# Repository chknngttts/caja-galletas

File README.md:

# caja-galletas

> *Caja de ruido en proceso*
>
> *Todas las versiones de KiCad están en sus carpetas propias*

-------------------

- ### Ideas y specs

> *La idea es tener esta PCB en una caja de galletas*
> 
> *La placa en sí ya tiene efectos integrados como reverb y un Muff Fuzz*
> 
> *La caja se conecta a un parlante o pc con Jack 3.5mm*
> 
> *Y como alimentación también cuenta con un Jack 3.5mm*
> 

  - Dentro de la caja hay:
    - Regulador de voltaje **``(9V -----> 5V)``**
      - VBUS
    - Reverb **``(PT2399)``**
      - *Switch para tener feedback*
    - Pre-Amp / Amp **``(TL072)``**
    - Muff Fuzz **``(2N5088)``**

-  ## **v2**

- ### esquematico v2

-  

-  El esqumatico del PT2399 es el "Boy in Well" con un mod de DIY Guitar Pedals:
    - https://youtu.be/9sHnaUfTWug?si=lqVHKw3zSinBoRW7&t=106 (1:46 - 4:46)
    - Muestra que cortando la conexión de un potenciómetro (RV7) con un switch y bajando el valor de una resistencia (R37), permite que la señal no se filtre (y no pierda info) para que llegue de vuelta al PT2399 haciendo repeats infinitos
      - https://www.diyguitarpedals.com.au/shop/boms/Boy%20in%20Well.pdf (Esquematico original sin switch) (Pagina 30)
    - En KiCad al hacer el ERC no me arroja errores
      - Solo 2 avisos de simbolos que modifiqué para hacer más facil el esquematico
      - En la PBC tampoco me muestra errores de conexión
        - Si quiero cambiar el tamaño y orden de la placa
          - Más rectangular y ahorrar espacio
         
-------------------
- Pre-Amp:         
  - 
  - El Amp que tomé de referencia, es el mismo que el de [maincra](https://github.com/disenoUDP/dis8644-2026-1-procesos-2/tree/main/00-proyecto-02/grupo-01)
    - Con los cambios para hacer más sensible el piezo (R4 y R5)
    - Eso sí, ahora usando ambos OP-Amps

- Muff Fuzz:
  - 
  - El efecto "Muff Fuzz" lo saqué de esta pagina:
    - https://beavisaudio.com/beavisboard/projects/bbp_MuffFuzz.pdf
 
-------------------

- ### pcb v2

- 
  - Tengo que arreglar las vías *(?)*
    - Sin querer use el tamaño predeterminado, no se si eso vaya a ser un problema
  - La huella de los 2N5088 y 78L05 tienen uno externo a la biblioteca de KiCad
    - Los cambié por uno de la biblioteca default en el v3
      - Además de corregir un alivio termico que no nombraban en los errores pero si era preocupante
- 
  - Hay espacio vacío que me permite re-ordenar los componentes y achicar el tamaño de la PCB
 
-------------------
 
- #### *v3 fueron arreglos minimos de huellas*

-------------------

- ## **v4**

- ### esquematico v4
  - 
    - igual que v2 pero con Jack 3.5mm a cambio del Terminal Block
 
-------------------
 
- ### pcb v4

- 
  - Cambié las vías al tamaño que nos recomendaros en taller
    - Optimicé la posición de los componentes para usar el espacio vacío
  - Añadí Mounting Holes M3
  - Al ver los errores solo mostraba problemas de la serigrafía
    - Nada con alivios termicos
- 
- 
  - Prefiero el color negro a rosado/morado

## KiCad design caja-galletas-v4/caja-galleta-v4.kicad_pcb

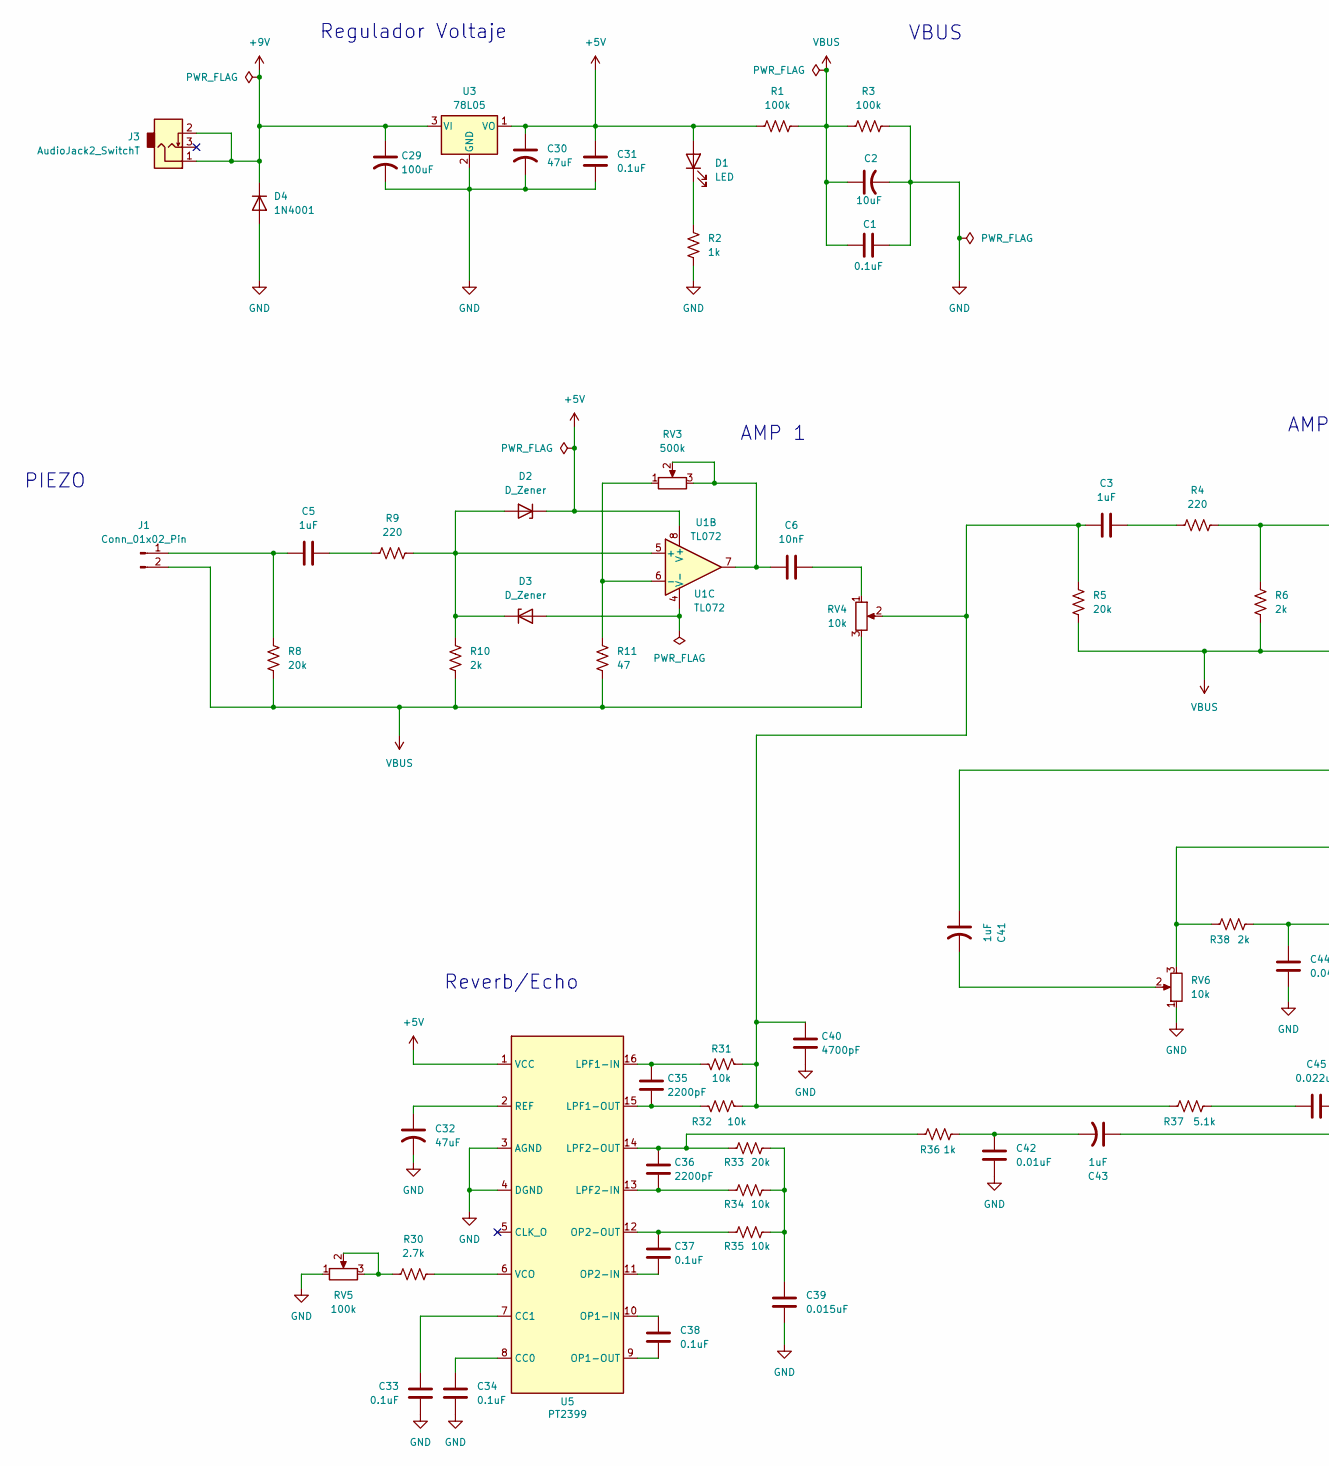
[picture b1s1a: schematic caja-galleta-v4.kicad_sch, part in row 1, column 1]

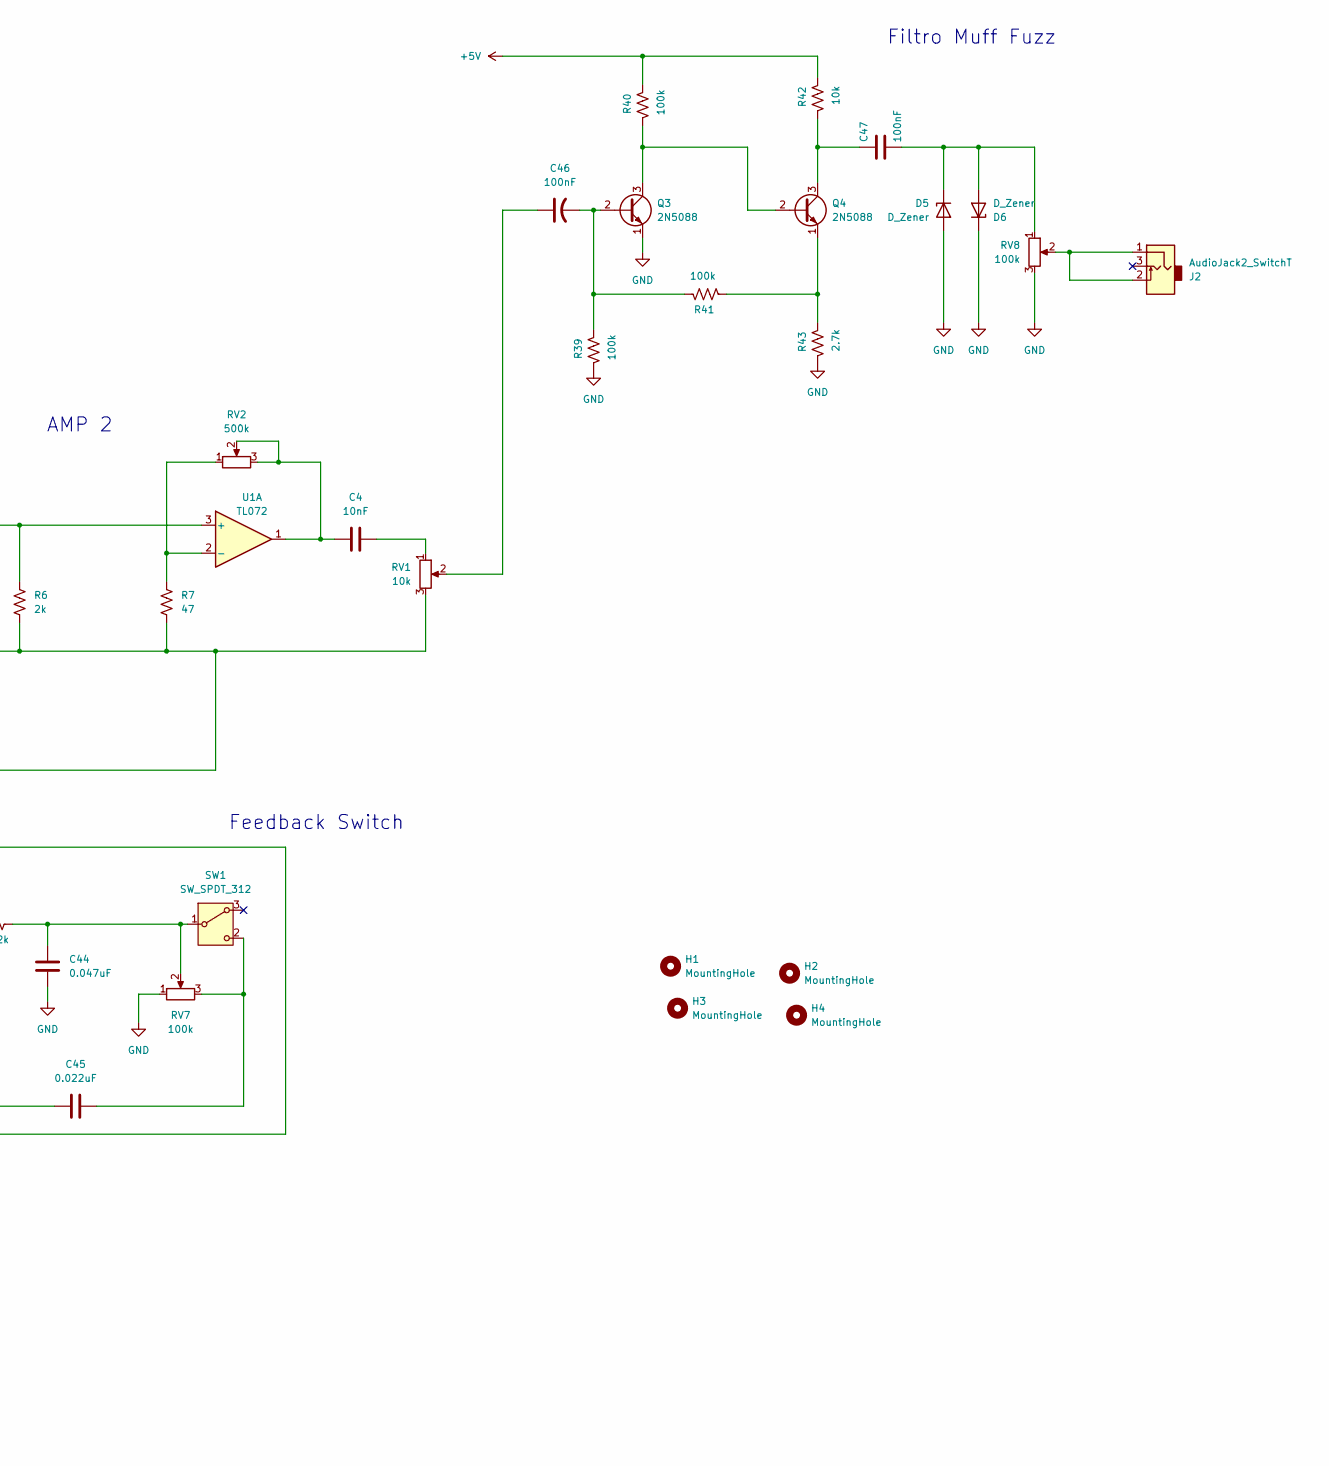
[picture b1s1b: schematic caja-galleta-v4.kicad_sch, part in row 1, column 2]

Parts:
C1, C31, C33, C34, C37, C38: 0.1uF; C_Disc_D3.8mm_W2.6mm_P2.50mm
C2: 10uF; CP_Radial_D5.0mm_P2.50mm
C3, C5: 1uF; C_Disc_D3.8mm_W2.6mm_P2.50mm
C4, C6: 10nF; C_Disc_D3.8mm_W2.6mm_P2.50mm
C29: 100uF; CP_Radial_D5.0mm_P2.50mm
C30, C32: 47uF; CP_Radial_D5.0mm_P2.50mm
C35, C36: 2200pF; C_Disc_D3.8mm_W2.6mm_P2.50mm
C39: 0.015uF; C_Disc_D3.8mm_W2.6mm_P2.50mm
C40: 4700pF; C_Disc_D3.8mm_W2.6mm_P2.50mm
C41, C43: 1uF; CP_Radial_D5.0mm_P2.50mm
C42: 0.01uF; C_Disc_D3.8mm_W2.6mm_P2.50mm
C44: 0.047uF; C_Disc_D3.8mm_W2.6mm_P2.50mm
C45: 0.022uF; C_Disc_D3.8mm_W2.6mm_P2.50mm
C46: 100nF; CP_Radial_D5.0mm_P2.50mm
C47: 100nF; C_Disc_D3.8mm_W2.6mm_P2.50mm
D1: LED; LED_D5.0mm
D2, D3, D5, D6: D_Zener; D_5W_P12.70mm_Horizontal
D4: 1N4001; D_5W_P12.70mm_Horizontal
H1, H2, H3, H4: MountingHole; MountingHole_3.2mm_M3
J1: Conn_01x02_Pin; PinSocket_1x02_P2.00mm_Vertical
J2, J3: AudioJack2_SwitchT; BarrelJack_Horizontal
Q3, Q4: 2N5088; TO-92
R1, R3, R39, R40, R41: 100k; R_Axial_DIN0207_L6.3mm_D2.5mm_P10.16mm_Horizontal
R2, R36: 1k; R_Axial_DIN0207_L6.3mm_D2.5mm_P10.16mm_Horizontal
R4, R9: 220; R_Axial_DIN0207_L6.3mm_D2.5mm_P10.16mm_Horizontal
R5, R8, R33: 20k; R_Axial_DIN0207_L6.3mm_D2.5mm_P10.16mm_Horizontal
R6, R10, R38: 2k; R_Axial_DIN0207_L6.3mm_D2.5mm_P10.16mm_Horizontal
R7, R11: 47; R_Axial_DIN0207_L6.3mm_D2.5mm_P10.16mm_Horizontal
R30, R43: 2.7k; R_Axial_DIN0207_L6.3mm_D2.5mm_P10.16mm_Horizontal
R31, R32, R34, R35, R42: 10k; R_Axial_DIN0207_L6.3mm_D2.5mm_P10.16mm_Horizontal
R37: 5.1k; R_Axial_DIN0207_L6.3mm_D2.5mm_P10.16mm_Horizontal
RV1, RV4, RV6: 10k; Potentiometer_Alps_RK163_Single_Horizontal
RV2, RV3: 500k; Potentiometer_Alps_RK163_Single_Horizontal
RV5, RV7, RV8: 100k; Potentiometer_Alps_RK163_Single_Horizontal
SW1: SW_SPDT_312; SW_Slide-03_Wuerth-WS-SLTV_10x2.5x6.4_P2.54mm
U1: TL072; DIP-8_W7.62mm_Socket_LongPads
U3: 78L05; TO-92
U5: PT2399; DIP-16_W10.16mm_LongPads

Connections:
+5V: C30.1, C31.1, D1.2 (A), D2.1 (K), R1.1, R40.2, R42.2, U1.8 (V+), U3.1 (VO), U5.1 (VCC)
+9V: C29.1, D4.1 (K), J3.1, J3.2, U3.3 (VI)
GND: C1.2, C2.2, C29.2, C30.2, C31.2, C32.2, C33.2, C34.2, C39.2, C40.2, C42.2, C44.1, D4.2 (A), D5.2 (A), D6.1 (K), Q3.1 (E), R2.1, R3.2, R39.1, R43.1, RV5.1, RV6.1, RV7.1, RV8.3, U3.2 (GND), U5.3 (AGND), U5.4 (DGND)
unnamed: C3.1, C40.1, R5.2, R31.2, R32.2, R37.1, RV4.2
unnamed: C3.2, R4.2
unnamed: C4.1, RV2.2, RV2.3, U1.1
unnamed: C4.2, RV1.1
unnamed: C5.2, R9.2
unnamed: C6.1, RV3.2, RV3.3, U1.7
unnamed: C6.2, RV4.1
unnamed: C39.1, R33.2, R34.2, R35.2
unnamed: C41.2, RV6.2
unnamed: C42.1, C43.2, R36.2
unnamed: C43.1, R38.1, RV6.3
unnamed: C45.1, R37.2
unnamed: C46.1, RV1.2
unnamed: D1.1 (K), R2.2
unnamed: D2.2 (A), D3.1 (K), R9.1, R10.2, U1.5 (+)
unnamed: D3.2 (A), U1.4 (V-)
unnamed: C47.1, D5.1 (K), D6.2 (A), RV8.1
unnamed: C5.1, J1.1, R8.2
unnamed: J2.1, J2.2, RV8.2
unnamed: C46.2, Q3.2 (B), R39.2, R41.2
unnamed: Q3.3 (C), Q4.2 (B), R40.1
unnamed: C47.2, Q4.3 (C), R42.1
unnamed: Q4.1 (E), R41.1, R43.2
unnamed: R30.1, RV5.2, RV5.3
unnamed: C44.2, R38.2, RV7.2, SW1.1 (B)
unnamed: C45.2, RV7.3, SW1.2 (C)
unnamed: R4.1, R6.2, U1.3 (+)
unnamed: R7.2, RV2.1, U1.2 (-)
unnamed: R11.2, RV3.1, U1.6 (-)
unnamed: C34.1, U5.8 (CC0)
unnamed: C33.1, U5.7 (CC1)
unnamed: C35.1, R31.1, U5.16 (LPF1-IN)
unnamed: C35.2, R32.1, U5.15 (LPF1-OUT)
unnamed: C36.2, R34.1, U5.13 (LPF2-IN)
unnamed: C36.1, R33.1, R36.1, U5.14 (LPF2-OUT)
unnamed: C38.1, U5.10 (OP1-IN)
unnamed: C38.2, U5.9 (OP1-OUT)
unnamed: C37.2, U5.11 (OP2-IN)
unnamed: C37.1, R35.1, U5.12 (OP2-OUT)
unnamed: C32.1, U5.2 (REF)
unnamed: R30.2, U5.6 (VCO)
VBUS: C1.1, C2.1, C41.1, J1.2, R1.2, R3.1, R5.1, R6.1, R7.1, R8.1, R10.1, R11.1, RV1.3, RV4.3

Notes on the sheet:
AMP 1
Regulador Voltaje
Filtro Muff Fuzz
Feedback Switch
Reverb/Echo
AMP 2
PIEZO
VBUS

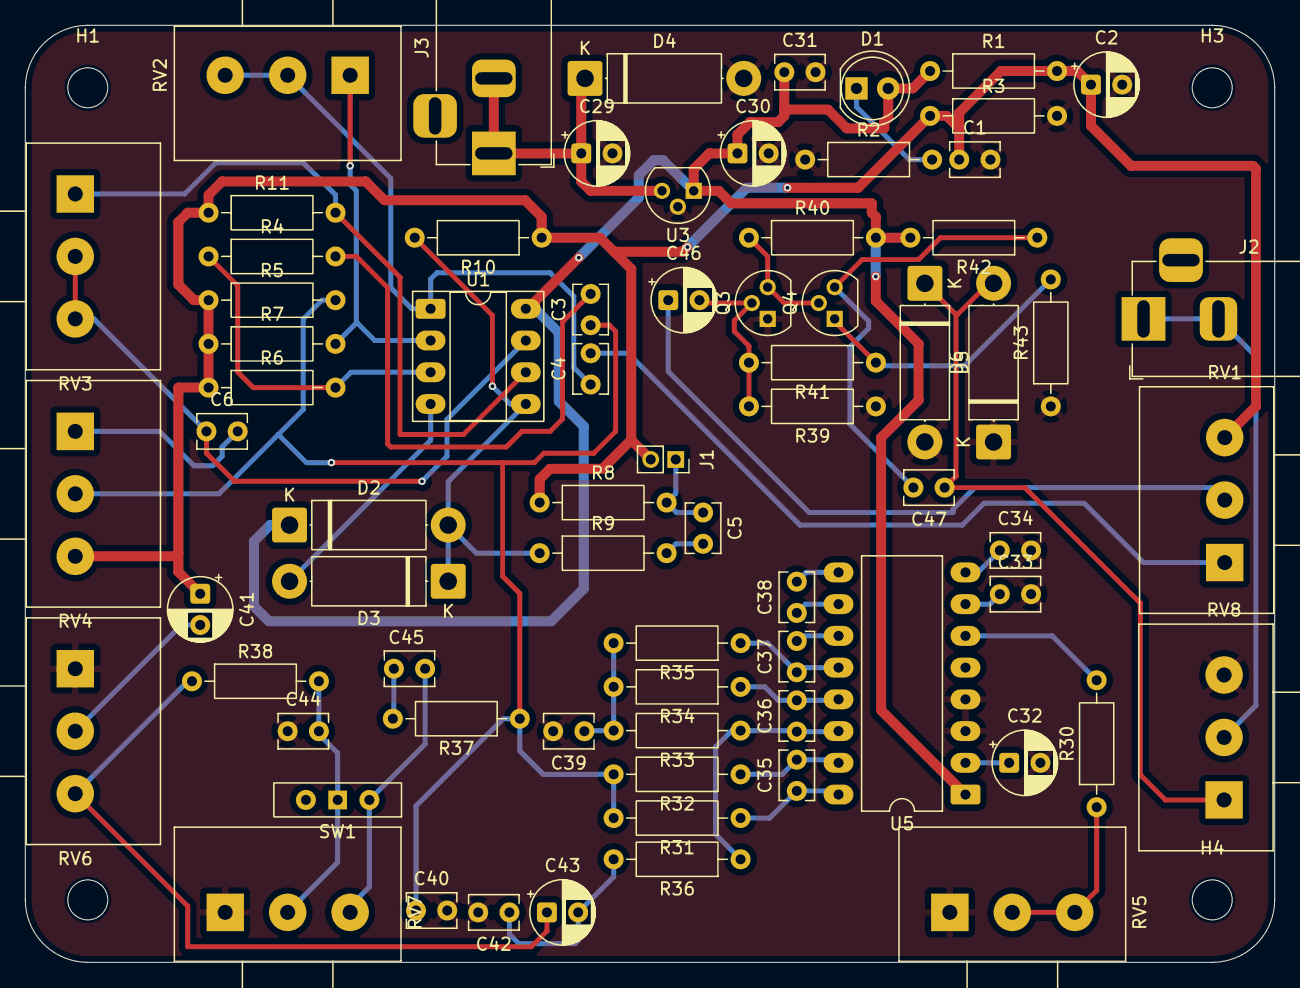
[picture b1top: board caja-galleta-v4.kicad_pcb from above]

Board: 2 copper layers, 100.0 x 75.0 mm, 77 parts (0 on the bottom side), 45 nets.

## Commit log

2026-06-07 carpeta-v1
2026-06-07 borrar-lol
2026-06-07 imagenes
2026-06-07 imagenes-v2
2026-06-07 resize
2026-06-07 resize-correcto
2026-06-07 v2-texto
2026-06-07 reintento-imagen
2026-06-07 reintento-imagen-2
2026-06-07 pre-amp
2026-06-07 arreglos-y-v3
2026-06-07 titulos-filtro
2026-06-11 v4-imagenes
2026-06-11 imagen
2026-06-11 imagen-v4
2026-06-11 v4-avance
2026-06-12 size
2026-06-12 imagenes-v4-tamaño-real
2026-06-12 muff-fuzz
2026-06-12 tamaño
